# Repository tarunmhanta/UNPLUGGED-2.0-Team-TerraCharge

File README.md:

# 🚀 UNPLUGGED 2.0

## Round 2

## 🔷 Team: TerraCharge
**Members:**
- Tarun Mhanta  
- Pravin Fulpati  
- Nikhileshwar Adam  
- Suyash Parkhe  
- Prajakta Patil  
- Vaishali Waghmare  

---

## 📌 Project Overview
**TerraCharge** is an innovative project developed for the **UNPLUGGED 2.0** competition. It integrates various environmental, electrical, and automation sensors into a **smart, sustainable energy monitoring system** powered by solar energy. The system is built using an **ESP32 microcontroller**, multiple sensors, and a rechargeable power module to collect and analyze real-time environmental data.

### 🌟 Features
- **Solar-powered energy monitoring**
- **Real-time environmental data collection**
- **Multi-sensor integration with ESP32**
- **Smart automation with relay control**
- **Low-power IoT-enabled system**

---

## 📋 Bill of Materials (BOM)
### Components Used:

| # | **Component Name** |
|---|--------------------|
| 1 | ESP32-53 Dev Module |
| 2 | MQ-135 Gas Sensor |
| 3 | Sound Sensor Module |
| 4 | OLED Display |
| 5 | BME280 Environmental Sensor |
| 6 | Solar Panel |
| 7 | Rechargeable Module (TP4065) |
| 8 | Battery 3.7V 2500mAh 18650 |
| 9 | Voltage Booster |
| 10 | Dust Sensor |
| 11 | Hall Effect Sensor |
| 12 | MAX471 Current & Voltage Sensor |
| 13 | Water Flow Sensor |
| 14 | DHT11 Temperature & Humidity Sensor |
| 15 | Soil Moisture Sensor |
| 16 | Relay Module |
| 17 | Rain Sensor |
| 18 | RTC DS3231 Module |
| 19 | IR Flame Sensor |

---

## 🛠️ PCB Design
The **Printed Circuit Board (PCB)** layout includes:
- **Complete PCB Layout** 🔄
- **Front Copper Layout** 🔆
- **Back Copper Layout** 🔶
- **3D Rendered Image of PCB** 🏗️
- **Schematic Diagram Screenshot** 🖥️

---

## ✅ Verification Checklist
- [ ] **BOM Verification** ✔️
- [ ] **Component Testing** 🛠️
- [ ] **Circuit Debugging** 🧐
- [ ] **Code Upload & Testing** 💻
- [ ] **Final Prototype Testing** 🚀

---

## 📂 GitHub Repository
This repository contains:
- 🖥️ **Source code for ESP32 integration**
- 📟 **Sensor interfacing scripts**
- 📊 **PCB schematics and layouts**
- 📄 **Project documentation**

### 📌 How to Use This Repository?
1. **Clone the repository**:  
   ```sh
   git clone https://github.com/tarunmhanta/UNPLUGGED-2.0-Team-TerraCharge.git
   ```
2. **Navigate to the project directory**:  
   ```sh
   cd unplugged-2.0-terracharge
   ```
3. **Run the setup scripts** and upload code to ESP32.

---

## 📞 Contact Us
For any queries or collaboration, feel free to reach out to **Team TerraCharge**.  
📧 Email: [tarunmhanta1@gmail.com](tarunmhanta1@gmail.com)  
---

🚀 **"Innovate, Sustain, and Charge the Future!"** 🔋

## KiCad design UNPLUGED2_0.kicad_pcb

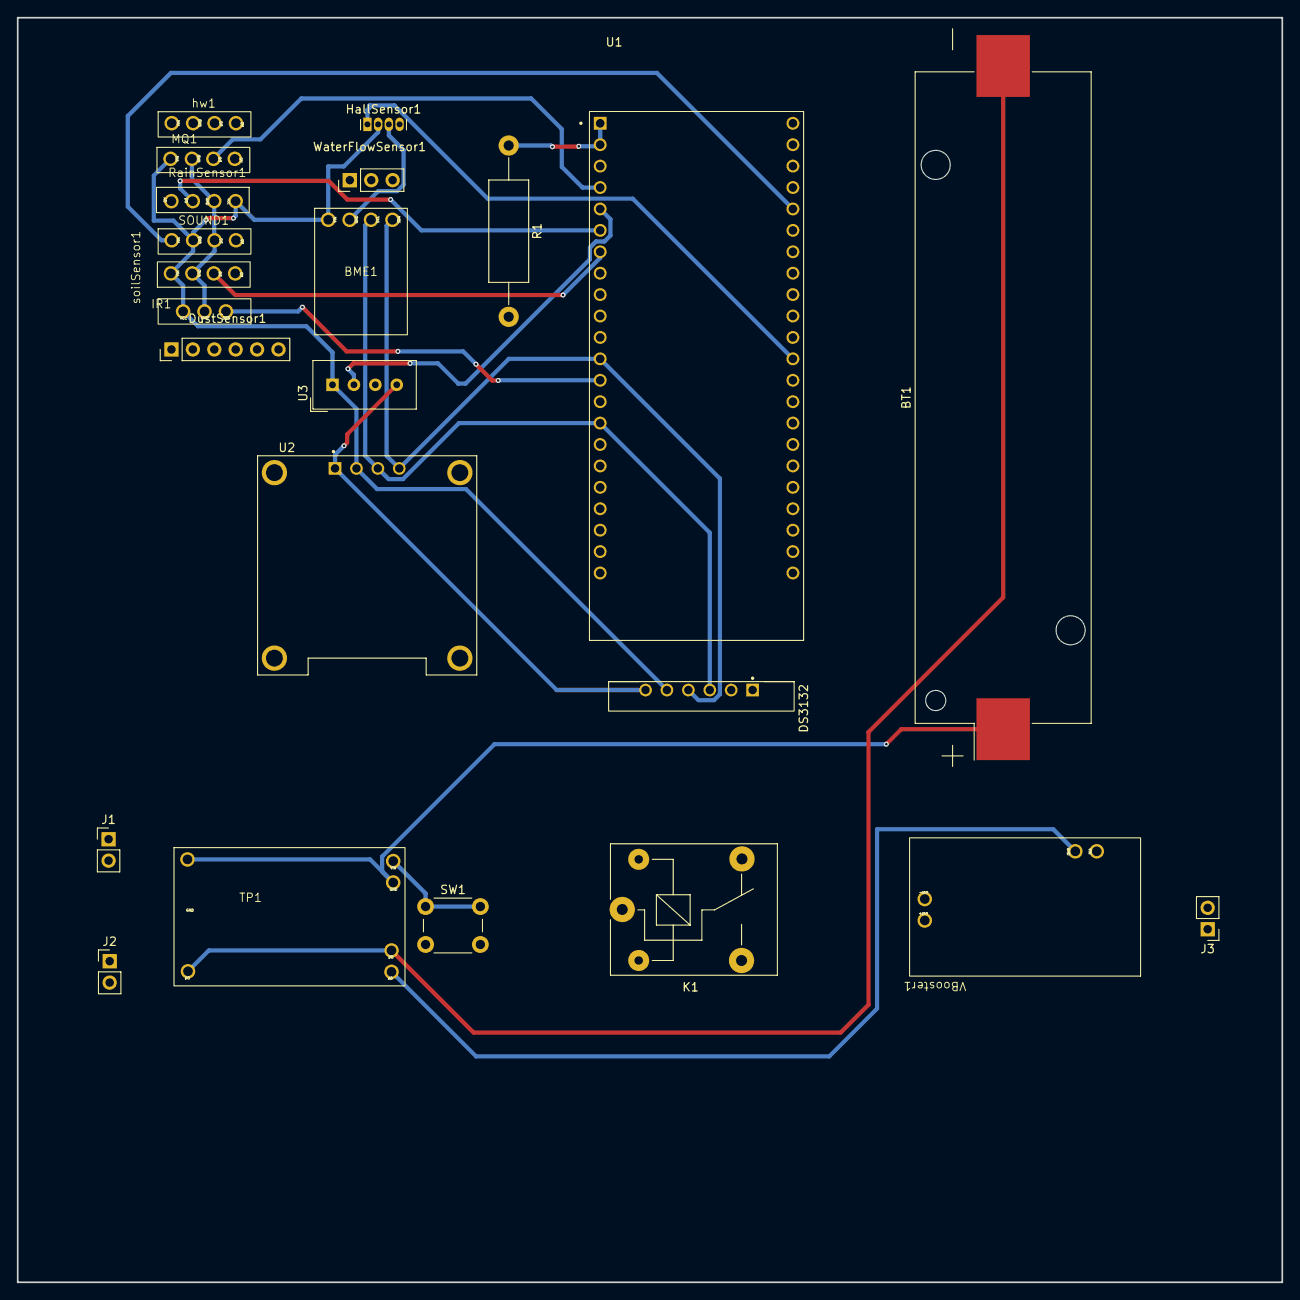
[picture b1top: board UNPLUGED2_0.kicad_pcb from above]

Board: 2 copper layers, 150.0 x 150.0 mm, 23 parts (0 on the bottom side), 17 nets.

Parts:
BME1: BME280; Untitled
BT1: Battery_Cell; BatteryHolder_Keystone_1042_1x18650
DS3132: DS3231; MODULE_TC00500
DustSensor1: Conn_01x06_Pin; PinHeader_1x06_P2.54mm_Vertical
HallSensor1: Allegro_SIP-4
IR1: Untitled
J1: SOLAR; PinHeader_1x02_P2.54mm_Vertical
J2: BCharge; PinHeader_1x02_P2.54mm_Vertical
J3: Alive; PinHeader_1x02_P2.54mm_Vertical
K1: Relay_SPDT; Relay_SPDT_SANYOU_SRD_Series_Form_C
MQ1: Untitled
R1: 150; R_Axial_DIN0414_L11.9mm_D4.5mm_P20.32mm_Horizontal
RainSensor1: Untitled
SOUND1: HW484
SW1: SW_Push; SW_PUSH_6mm_H4.3mm
TP1: Untitled
U1: ESP32-S3-DEVKITC-1-N8R2; XCVR_ESP32-S3-DEVKITC-1-N8R2
U2: DM-OLED096-636; MODULE_DM-OLED096-636
U3: DHT11; Aosong_DHT11_5.5x12.0_P2.54mm
VBooster1: Untitled
WaterFlowSensor1: Conn_01x03_Pin; PinHeader_1x03_P2.54mm_Vertical
hw1: Untitled
soilSensor1: SoilSensor

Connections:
DHT: U1.J1_5 (GPIO5), U3.2 (DATA)
Dust+: R1.1, U1.J1_1 (3V3), U1.J1_2 (3V3)
Dust-: U1.J1_22 (GND), U1.J3_1 (GND), U1.J3_21 (GND), U1.J3_22 (GND)
GND: BME1.2 (GND), DS3132.6 (GND), HallSensor1.3 (GND), IR1.2 (GND), MQ1.2 (GND), RainSensor1.2 (GND), SOUND1.3 (GND), U2.1 (GND), U3.4 (GND), soilSensor1.2 (GND)
Hall: HallSensor1.1 (DO), U1.J3_12 (GPIO36)
IR: IR1.3 (OUT), U1.J1_13 (GPIO3)
MQ1: MQ1.3 (D0), U1.J1_4 (GPIO4)
unnamed: BT1.1 (+), TP1.2 (B+)
unnamed: BT1.2 (-), TP1.3 (B-)
unnamed: SW1.1, TP1.1 (OUT+)
Rain: RainSensor1.3 (D0), U1.J1_6 (GPIO6)
SCL: BME1.3 (SCL), DS3132.3 (SCL), U1.J1_15 (GPIO9), U2.3 (SCL)
SDA: BME1.4 (SDA), DS3132.4 (SDA), U1.J1_12 (GPIO8), U2.4 (SDA)
Soil: U1.J1_7 (GPIO7), soilSensor1.3 (D0)
Sound: SOUND1.1 (DO), U1.J3_5 (GPIO2)
V-: TP1.4 (OUT-), VBooster1.2 (OUT-)
VCC: BME1.1 (VIN), DS3132.5 (VCC), HallSensor1.2 (VCC), IR1.1 (VCC), MQ1.1 (VCC), RainSensor1.1 (VCC), SOUND1.2 (VCC), U2.2 (VCC_IN), U3.1 (VDD), soilSensor1.1 (VCC)
